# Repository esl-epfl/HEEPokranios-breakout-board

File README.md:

# This repository contains the HEEPokranios breakout board

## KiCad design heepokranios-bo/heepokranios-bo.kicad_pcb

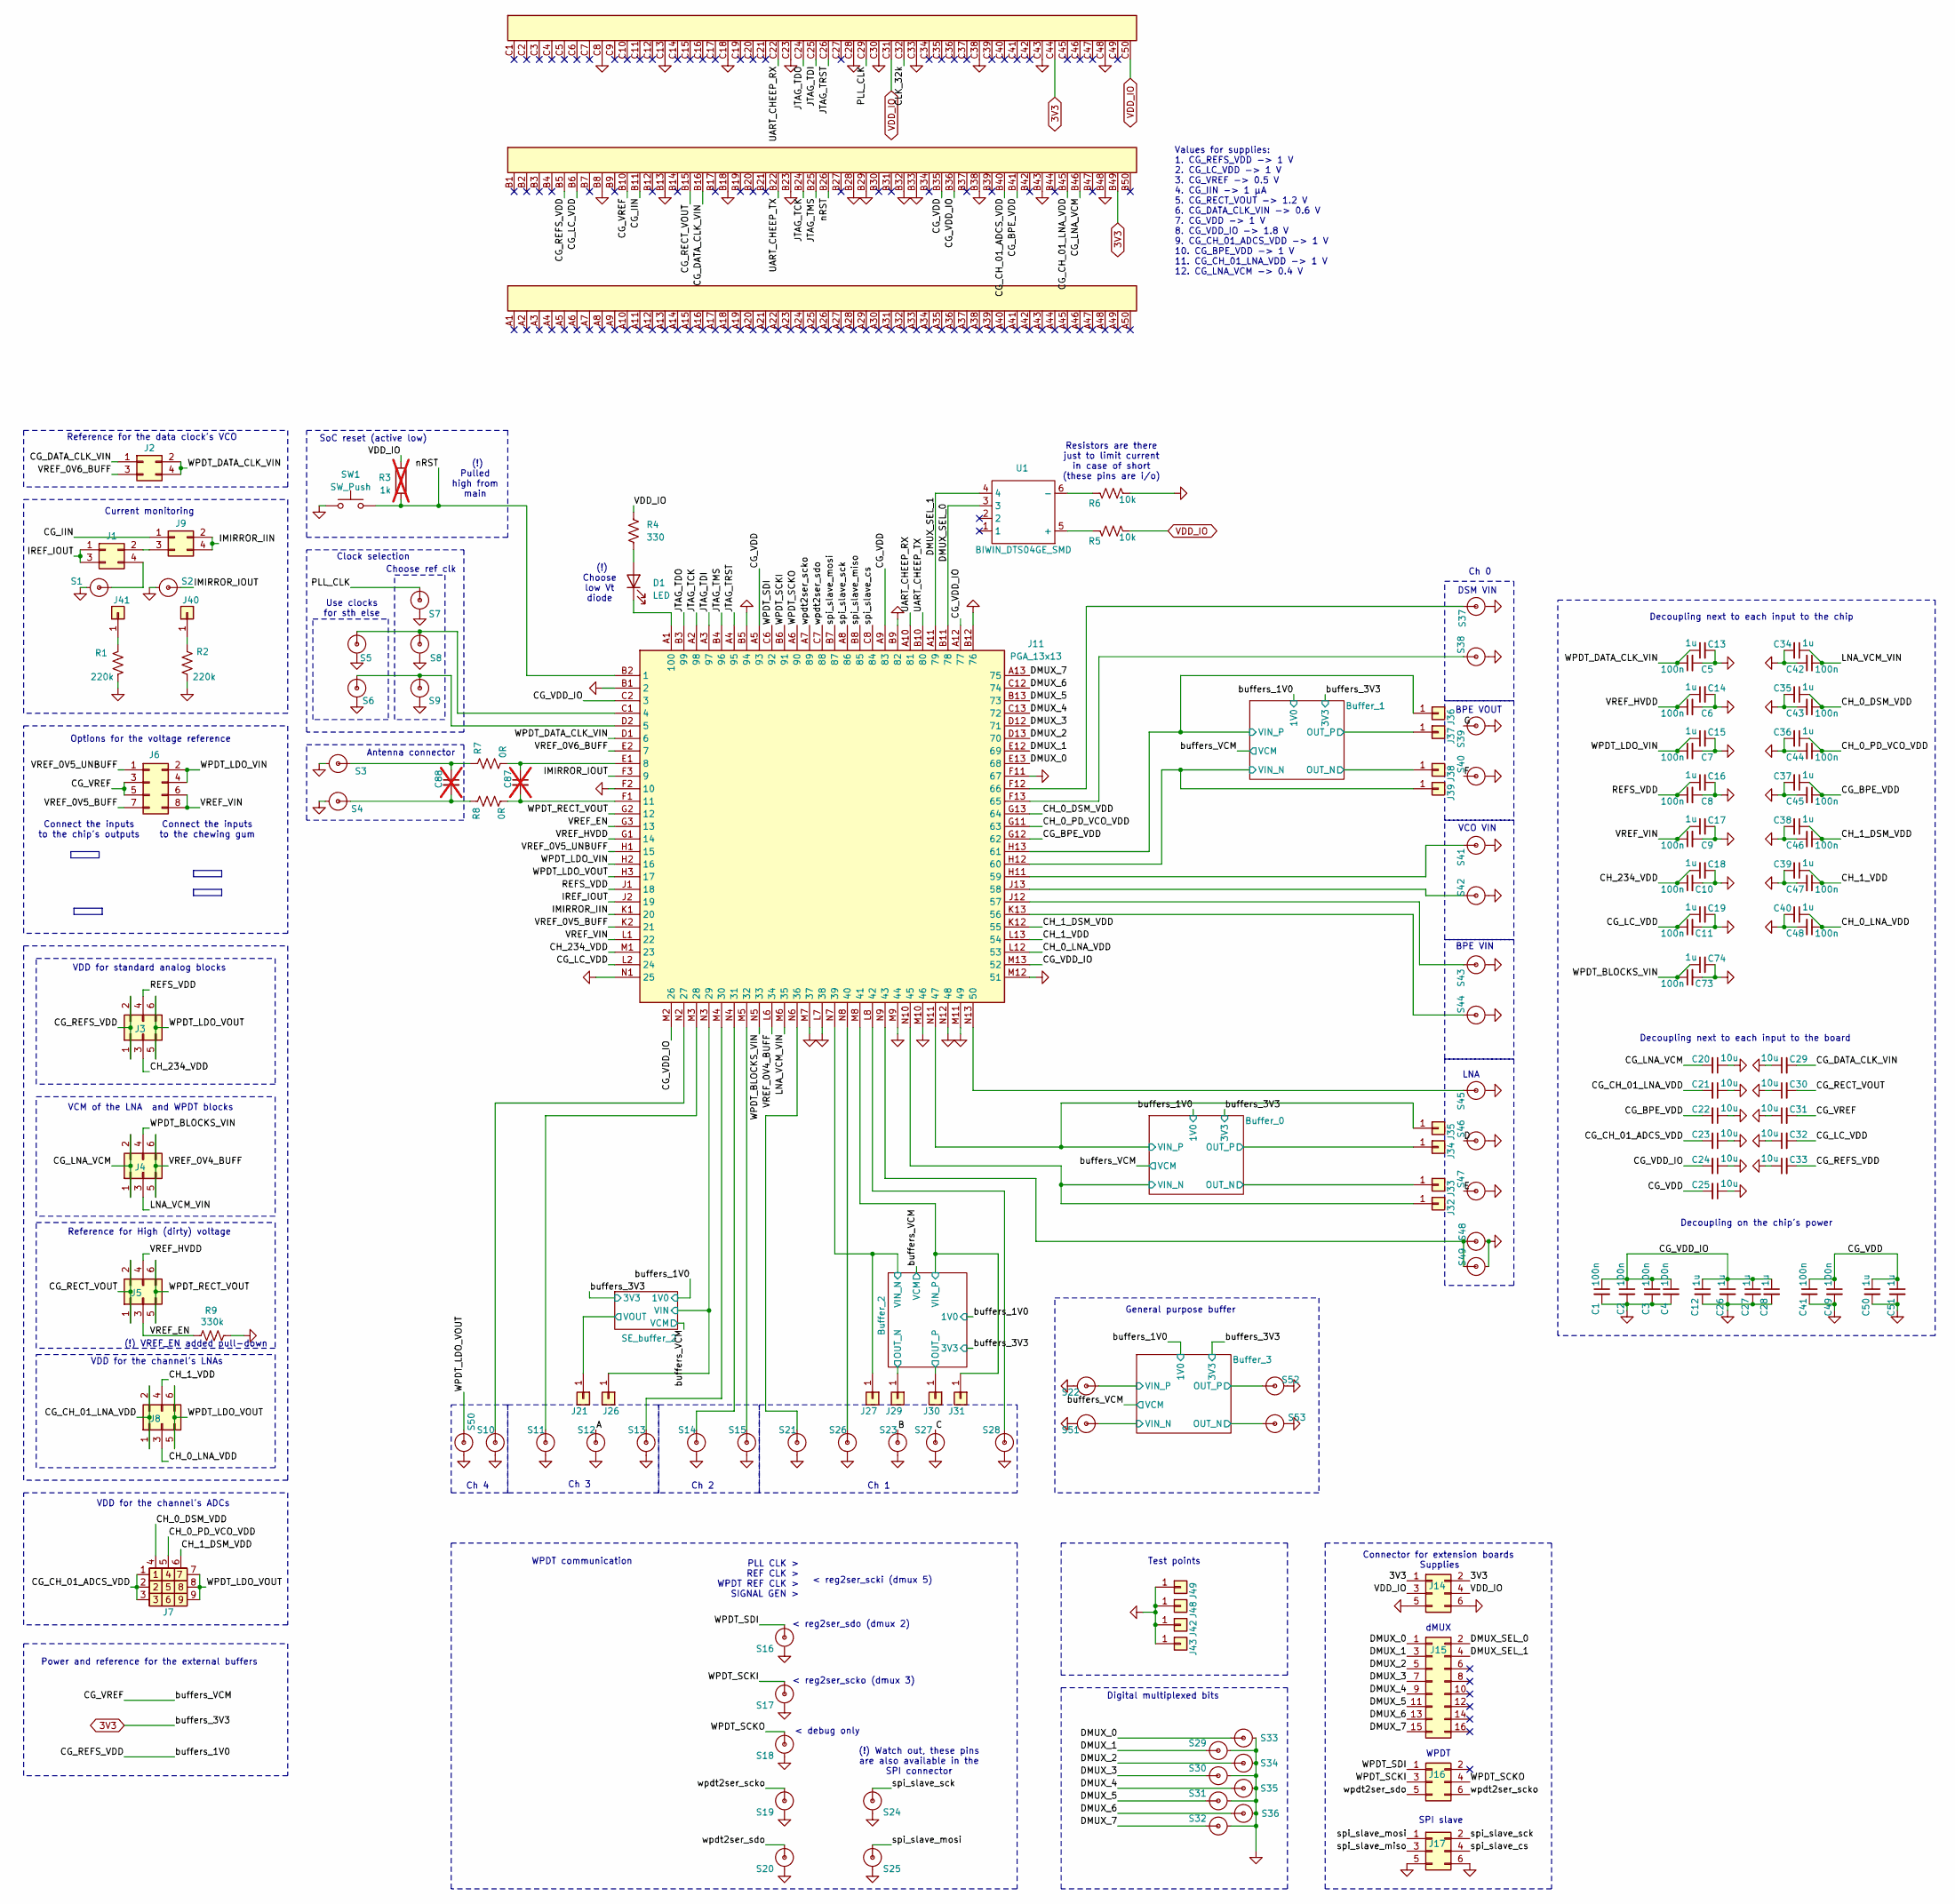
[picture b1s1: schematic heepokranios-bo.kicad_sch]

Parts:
C1, C2, C3, C4, C5, C6, C7, C8, C9, C10, C11, C41, C42, C43, C44, C45, C46, C47, C48, C49, C73: 100n; C_0603_1608Metric; Mouser Part Number 80-C0805C104Z3V; Digikey Part Number 399-9158-1-ND
C12, C13, C14, C15, C16, C17, C18, C19, C26, C27, C28, C34, C35, C36, C37, C38, C39, C40, C50, C51, C74: 1u; C_0603_1608Metric; Mouser Part Number 80-C0805C104Z3V; Digikey Part Number 399-9158-1-ND
C20, C21, C22, C23, C24, C25, C29, C30, C31, C32, C33: 10u; C_0603_1608Metric; Mouser Part Number 80-C0805C104Z3V; Digikey Part Number 399-9158-1-ND
C87, C88: C_0805_2012Metric_Pad1.18x1.45mm_HandSolder; Mouser Part Number 80-C0805C104Z3V; Digikey Part Number 399-9158-1-ND; not fitted
D1: LED; LED_0603_1608Metric
J1, J2, J9: Conn_02x02_Odd_Even; PinHeader_2x02_P2.54mm_Vertical
J3, J4, J5, J8: Conn_02x03_Odd_Even; PinHeader_2x03_P2.54mm_Vertical
J6: Conn_02x04_Odd_Even; PinHeader_2x04_P2.54mm_Vertical
J7: Conn_3x03
J10: cheep_board_connector
J11: PGA_13x13; Mouser Part Number 535-100-PGM13061-10
J14, J16, J17: Conn_02x03_Odd_Even; PinSocket_2x03_P2.54mm_Horizontal
J15: Conn_02x08_Odd_Even; PinSocket_2x08_P2.54mm_Horizontal
J21, J26, J27, J29, J30, J31, J32, J33, J34, J35, J36, J37, J38, J39, J40, J41, J42, J43, J48, J49: Conn_01x02; PinHeader_1x01_P2.54mm_Vertical
R1, R2: 220k; R_0603_1608Metric
R3: 1k; R_0603_1608Metric; LCSC C21190; not fitted
R4: 330; R_0603_1608Metric
R5, R6: 10k; R_0603_1608Metric
R7, R8: 0R; R_0603_1608Metric
R9: 330k; R_0603_1608Metric
S1, S2, S3, S4, S5, S6, S7, S8, S9, S10, S11, S12, S13, S14, S15, S16, S17, S18, S19, S20, S21, S22, S23, S24, S25, S26, S27, S28, S29, S30, S31, S32, S33, S34, S35, S36, S37, S38, S39, S40, S41, S42, S43, S44, S45, S46, S47, S48, S49, S50, S51, S52, S53: SMA connector; SMA_w_tp
SW1: SW_Push; SW_Push_1P1T_NO_CK_KMR2
U1: BIWIN_DTS04GE_SMD; lcsc C3294670

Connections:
3V3: J10.B49, J10.C44, J14.1, J14.2; also elsewhere on the board
/A: S12.1
/B: S23.1
/Buffer_0/OUT_N: J33.1 (Pin_1_1); also elsewhere on the board
/Buffer_0/OUT_P: J34.1 (Pin_1_1); also elsewhere on the board
/Buffer_0/VIN_N: J11.N10 (45), J32.1 (Pin_1_1); also elsewhere on the board
/Buffer_0/VIN_P: J11.N11 (47), J35.1 (Pin_1_1); also elsewhere on the board
/Buffer_1/OUT_N: J38.1 (Pin_1_1); also elsewhere on the board
/Buffer_1/OUT_P: J37.1 (Pin_1_1); also elsewhere on the board
/Buffer_1/VIN_N: J11.H12 (60), J39.1 (Pin_1_1); also elsewhere on the board
/Buffer_1/VIN_P: J11.H13 (61), J36.1 (Pin_1_1); also elsewhere on the board
/Buffer_2/OUT_N: J29.1 (Pin_1_1); also elsewhere on the board
/Buffer_2/OUT_P: J30.1 (Pin_1_1); also elsewhere on the board
/Buffer_2/VIN_N: J11.N7 (39), J27.1 (Pin_1_1); also elsewhere on the board
/Buffer_2/VIN_P: J11.M8 (41), J31.1 (Pin_1_1); also elsewhere on the board
/Buffer_3/OUT_N: S53.1; also elsewhere on the board
/Buffer_3/OUT_P: S52.1; also elsewhere on the board
/Buffer_3/VIN_N: S51.1; also elsewhere on the board
/Buffer_3/VIN_P: S22.1; also elsewhere on the board
/C: S27.1
/CG_BPE_VDD: C22.2, C37.1, C45.1, J10.B41, J11.G12 (62)
/CG_CH_01_ADCS_VDD: C23.2, J7.1, J7.2, J7.3, J10.B40
/CG_CH_01_LNA_VDD: C21.2, J8.1, J8.2, J10.B45
/CG_DATA_CLK_VIN: C29.2, J2.1, J10.B16
/CG_IIN: J9.1, J10.B11
/CG_LC_VDD: C11.1, C19.1, C32.2, J10.B6, J11.L2 (24)
/CG_LNA_VCM: C20.2, J4.1, J4.2, J10.B46
/CG_RECT_VOUT: C30.2, J5.1, J5.2, J10.B15
/CG_REFS_VDD: C33.2, J3.1, J3.2, J10.B5; also elsewhere on the board
/CG_VDD: C25.2, C41.1, C49.1, C50.1, C51.1, J10.B35, J11.A5 (93), J11.A9 (83)
/CG_VDD_IO: C1.1, C2.1, C3.1, C4.1, C12.1, C24.2, C26.1, C27.1, C28.1, J10.B36, J11.A12 (77), J11.C2 (3), J11.M2 (26), J11.M13 (52)
/CG_VREF: C31.2, J6.3, J6.5, J10.B10; also elsewhere on the board
/CH_0_DSM_VDD: C35.1, C43.1, J7.4, J11.G13 (64)
/CH_0_LNA_VDD: C40.1, C48.1, J8.3, J11.L12 (53)
/CH_0_PD_VCO_VDD: C36.1, C44.1, J7.5, J11.G11 (63)
/CH_1_DSM_VDD: C38.1, C46.1, J7.6, J11.K12 (55)
/CH_1_VDD: C39.1, C47.1, J8.4, J11.L13 (54)
/CH_234_VDD: C10.1, C18.1, J3.3, J11.M1 (23)
/CLK_32k: J10.C32
/D: S46.1
/DMUX_0: J11.E13 (68), J15.1, S33.1
/DMUX_1: J11.E12 (69), J15.3, S29.1
/DMUX_2: J11.D13 (70), J15.5, S34.1
/DMUX_3: J11.D12 (71), J15.7, S30.1
/DMUX_4: J11.C13 (72), J15.9, S35.1
/DMUX_5: J11.B13 (73), J15.11, S31.1
/DMUX_6: J11.C12 (74), J15.13, S36.1
/DMUX_7: J11.A13 (75), J15.15, S32.1
/DMUX_SEL_0: J11.B11 (78), J15.2, U1.3
/DMUX_SEL_1: J11.A11 (79), J15.4, U1.4
/E: S47.1
/F: S40.1
/G: S39.1
/IMIRROR_IIN: J9.2, J9.4, J11.K1 (20)
/IMIRROR_IOUT: J11.F3 (9), S2.1
/IREF_IOUT: J1.1, J1.3, J11.J2 (19)
/JTAG_TCK: J10.B24, J11.A2 (98)
/JTAG_TDI: J10.C25, J11.A3 (97)
/JTAG_TDO: J10.C24, J11.B3 (99)
/JTAG_TMS: J10.B25, J11.B4 (96)
/JTAG_TRST: J10.C26, J11.A4 (95)
/LNA_VCM_VIN: C34.1, C42.1, J4.3, J11.M6 (35)
/PLL_CLK: J10.C29, S7.1
/REFS_VDD: C8.1, C16.1, J3.4, J11.J1 (18)
/SE_buffer_2/VIN: J11.N3 (29), J26.1 (Pin_1_1); also elsewhere on the board
/SE_buffer_2/VOUT: J21.1 (Pin_1_1); also elsewhere on the board
/UART_CHEEP_RX: J10.C22, J11.A10 (81)
/UART_CHEEP_TX: J10.B22, J11.B10 (80)
/VREF_0V4_BUFF: J4.5, J4.6, J11.L6 (34)
/VREF_0V5_BUFF: J6.7, J11.K2 (21)
/VREF_0V5_UNBUFF: J6.1, J11.H1 (15)
/VREF_0V6_BUFF: J2.3, J11.E2 (7)
/VREF_EN: J5.3, J11.G3 (13), R9.1
/VREF_HVDD: C6.1, C14.1, J5.4, J11.G1 (14)
/VREF_VIN: C9.1, C17.1, J6.6, J6.8, J11.L1 (22)
/WPDT_BLOCKS_VIN: C73.1, C74.1, J4.4, J11.N5 (33)
/WPDT_DATA_CLK_VIN: C5.1, C13.1, J2.2, J2.4, J11.D1 (6)
/WPDT_LDO_VIN: C7.1, C15.1, J6.2, J6.4, J11.H2 (16)
/WPDT_LDO_VOUT: J3.5, J3.6, J7.7, J7.8, J7.9, J8.5, J8.6, J11.H3 (17), S50.1
/WPDT_RECT_VOUT: J5.5, J5.6, J11.G2 (12)
/WPDT_SCKI: J11.B6 (91), J16.3, S17.1
/WPDT_SCKO: J11.A6 (90), J16.4, S18.1
/WPDT_SDI: J11.C6 (92), J16.1, S16.1
/nRST: J10.B26, J11.B2 (1), R3.1, SW1.1
/spi_slave_cs: J11.C8 (84), J17.4
/spi_slave_miso: J11.B8 (85), J17.3
/spi_slave_mosi: J11.B7 (87), J17.1, S25.1
/spi_slave_sck: J11.A8 (86), J17.2, S24.1
/wpdt2ser_scko: J11.A7 (89), J16.6, S19.1
/wpdt2ser_sdo: J11.C7 (88), J16.5, S20.1
GND: C1.2, C2.2, C3.2, C4.2, C5.2, C6.2, C7.2, C8.2, C9.2, C10.2, C11.2, C12.2, C13.2, C14.2, C15.2, C16.2, C17.2, C18.2, C19.2, C20.1, C21.1, C22.1, C23.1, C24.1, C25.1, C26.2, C27.2, C28.2, C29.1, C30.1, C31.1, C32.1, C33.1, C34.2, C35.2, C36.2, C37.2, C38.2, C39.2, C40.2, C41.2, C42.2, C43.2, C44.2, C45.2, C46.2, C47.2, C48.2, C49.2, C50.2, C51.2, C73.2, C74.2, J10.B8, J10.B13, J10.B18, J10.B23, J10.B28, J10.B29, J10.B32, J10.B33, J10.B38, J10.B43, J10.B48, J10.C8, J10.C13, J10.C18, J10.C23, J10.C28, J10.C30, J10.C33, J10.C38, J10.C43, J10.C48, J11.B1 (2), J11.B5 (94), J11.B9 (82), J11.B12 (76), J11.F2 (10), J11.F11 (67), J11.L7 (38), J11.M7 (37), J11.M9 (44), J11.M10 (46), J11.M11 (49), J11.M12 (51), J11.N1 (25), J11.N12 (48), J14.5, J14.6, J17.5, J17.6, J42.1 (Pin_1_1), J43.1 (Pin_1_1), J48.1 (Pin_1_1), J49.1 (Pin_1_1), R1.2, R2.2, R6.2, R9.2, S1.2, S2.2, S3.2, S4.2, S5.2, S6.2, S7.2, S8.2, S9.2, S10.2, S11.2, S12.2, S13.2, S14.2, S15.2, S16.2, S17.2, S18.2, S19.2, S20.2, S21.2, S22.2, S23.2, S24.2, S25.2, S26.2, S27.2, S28.2, S29.2, S30.2, S31.2, S32.2, S33.2, S34.2, S35.2, S36.2, S37.2, S38.2, S39.2, S40.2, S41.2, S42.2, S43.2, S44.2, S45.2, S46.2, S47.2, S48.2, S49.2, S50.2, S51.2, S52.2, S53.2, SW1.2; also elsewhere on the board
unnamed: C88.1, R7.1, S3.1
unnamed: C88.2, R8.1, S4.1
unnamed: D1.2 (A), R4.2
unnamed: D1.1 (K), J11.A1 (100)
unnamed: J1.2, J9.3
unnamed: J1.4, S1.1
unnamed: J11.C1 (4), S5.1, S8.1
unnamed: J11.D2 (5), S6.1, S9.1
unnamed: C87.1, J11.E1 (8), R7.2
unnamed: C87.2, J11.F1 (11), R8.2
unnamed: J11.N2 (27), S10.1
unnamed: J11.M3 (28), S11.1
unnamed: J11.M4 (30), S13.1
unnamed: J11.N4 (31), S14.1
unnamed: J11.M5 (32), S15.1
unnamed: J11.N6 (36), S21.1
unnamed: J11.N8 (40), S26.1
unnamed: J11.L8 (42), S28.1
unnamed: J11.N9 (43), S48.1, S49.1
unnamed: J11.N13 (50), S45.1
unnamed: J11.K13 (56), S44.1
unnamed: J11.J12 (57), S43.1
unnamed: J11.J13 (58), S42.1
unnamed: J11.H11 (59), S41.1
unnamed: J11.F13 (65), S38.1
unnamed: J11.F12 (66), S37.1
unnamed: J40.1 (Pin_1_1), R2.1
unnamed: J41.1 (Pin_1_1), R1.1
unnamed: R5.1, U1.5 (+)
unnamed: R6.1, U1.6 (-)
VDD_IO: J10.C31, J10.C50, J14.3, J14.4, R3.2, R4.1, R5.2

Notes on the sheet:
LNA
Ch 1
Values for supplies: 1. CG_REFS_VDD -> 1 V 2. CG_LC_VDD -> 1 V 3. CG_VREF -> 0.5 V 4. CG_IIN -> 1 μA 5. CG_RECT_VOUT -> 1.2 V 6. CG_DATA_CLK_VIN -> 0.6 V 7. CG_VDD -> 1 V 8. CG_VDD_IO -> 1.8 V 9. CG_CH_01_ADCS_VDD -> 1 V 10. CG_BPE_VDD -> 1 V 11. CG_CH_01_LNA_VDD -> 1 V 12. CG_LNA_VCM -> 0.4 V
Digital multiplexed bits
(!) Choose low Vt diode
Ch 0
Clock selection
Connector for extension boards
WPDT communication
SPI slave
VCM of the LNA and WPDT blocks
Decoupling on the chip's power
PLL CLK > REF CLK > WPDT REF CLK > SIGNAL GEN >
Test points
VDD for the channel's ADCs
BPE VOUT
< reg2ser_scki (dmux 5)
< reg2ser_sdo (dmux 2)
Use clocks for sth else
Power and reference for the external buffers
VDD for standard analog blocks
Options for the voltage reference
Choose ref clk
< reg2ser_scko (dmux 3)
Current monitoring
Ch 2
dMUX
Ch 4
Decoupling next to each input to the chip
BPE VIN
SoC reset (active low)
Ch 3
VCO VIN
DSM VIN
< debug only
VDD for the channel's LNAs
(!) VREF_EN added pull-down
Reference for the data clock's VCO
Connect the inputs to the chewing gum
WPDT

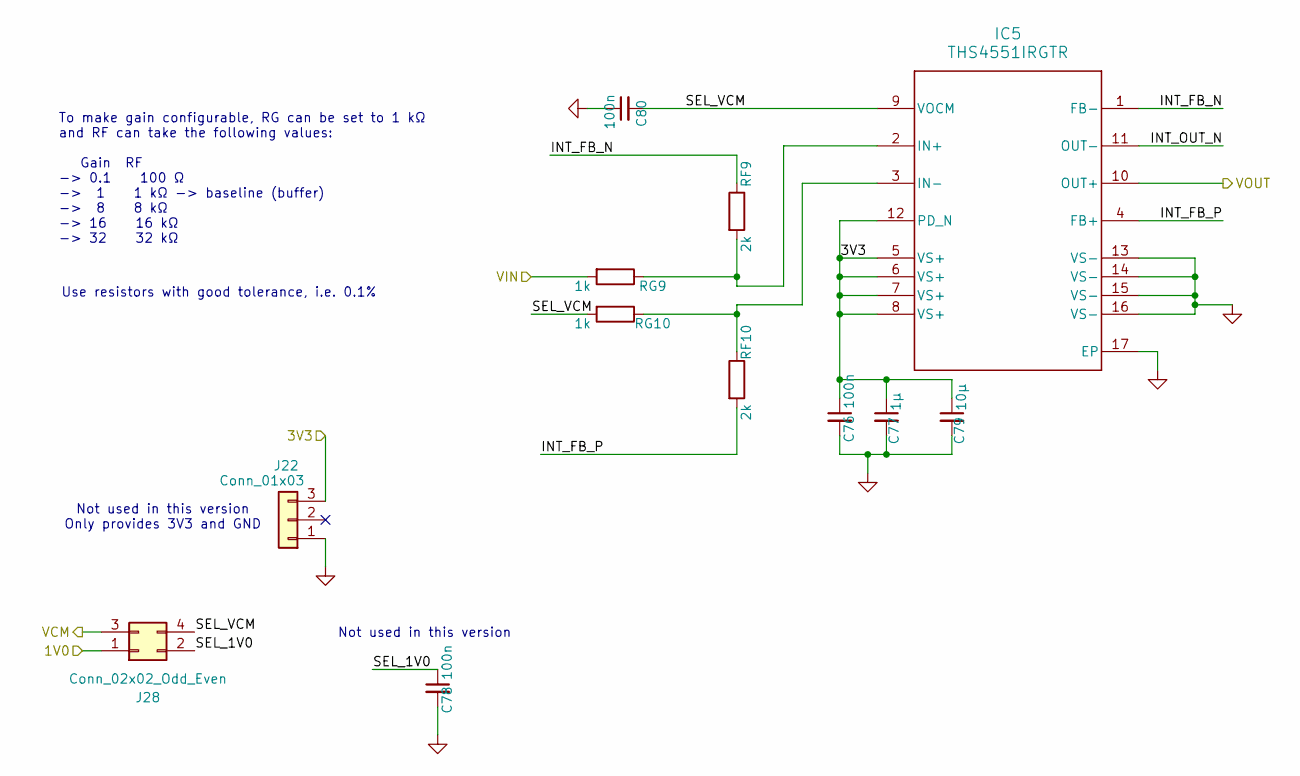
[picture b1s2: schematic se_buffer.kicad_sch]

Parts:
C76, C78, C80: 100n; C_0603_1608Metric; Mouser Part Number 80-C0805C104Z3V; Digikey Part Number 399-9158-1-ND
C77: 1μ; C_0603_1608Metric; Mouser Part Number 80-C0805C104Z3V; Digikey Part Number 399-9158-1-ND
C79: 10μ; C_0603_1608Metric; Mouser Part Number 80-C0805C104Z3V; Digikey Part Number 399-9158-1-ND
IC5: THS4551IRGTR; RGT0016C
J22: Conn_01x03; PinHeader_1x03_P2.54mm_Vertical
J28: Conn_02x02_Odd_Even; PinHeader_2x02_P2.54mm_Vertical
RF9, RF10: 2k; R_0603_1608Metric; LCSC C22975
RG9, RG10: 1k; R_0603_1608Metric; LCSC C22975

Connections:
3V3: C76.1, C77.1, C79.1, IC5.5 (VS+), IC5.6 (VS+), IC5.7 (VS+), IC5.8 (VS+), IC5.12 (PD_N), J22.3; also elsewhere on the board
/CG_REFS_VDD: J28.1; also elsewhere on the board
/CG_VREF: J28.3; also elsewhere on the board
/SE_buffer_2/INT_FB_N: IC5.1 (FB-), RF9.1
/SE_buffer_2/INT_FB_P: IC5.4 (FB+), RF10.2
/SE_buffer_2/INT_OUT_N: IC5.11 (OUT-)
/SE_buffer_2/SEL_1V0: C78.1, J28.2
/SE_buffer_2/SEL_VCM: C80.2, IC5.9 (VOCM), J28.4, RG10.2
/SE_buffer_2/VIN: RG9.2; also elsewhere on the board
/SE_buffer_2/VOUT: IC5.10 (OUT+); also elsewhere on the board
GND: C76.2, C77.2, C78.2, C79.2, C80.1, IC5.13 (VS-), IC5.14 (VS-), IC5.15 (VS-), IC5.16 (VS-), IC5.17 (EP), J22.1; also elsewhere on the board
unnamed: IC5.2 (IN+), RF9.2, RG9.1
unnamed: IC5.3 (IN-), RF10.1, RG10.1

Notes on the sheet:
To make gain configurable, RG can be set to 1 kΩ and RF can take the following values: Gain RF -> 0.1 100 Ω -> 1 1 kΩ -> baseline (buffer) -> 8 8 kΩ -> 16 16 kΩ -> 32 32 kΩ
Not used in this version Only provides 3V3 and GND
Not used in this version
Use resistors with good tolerance, i.e. 0.1%

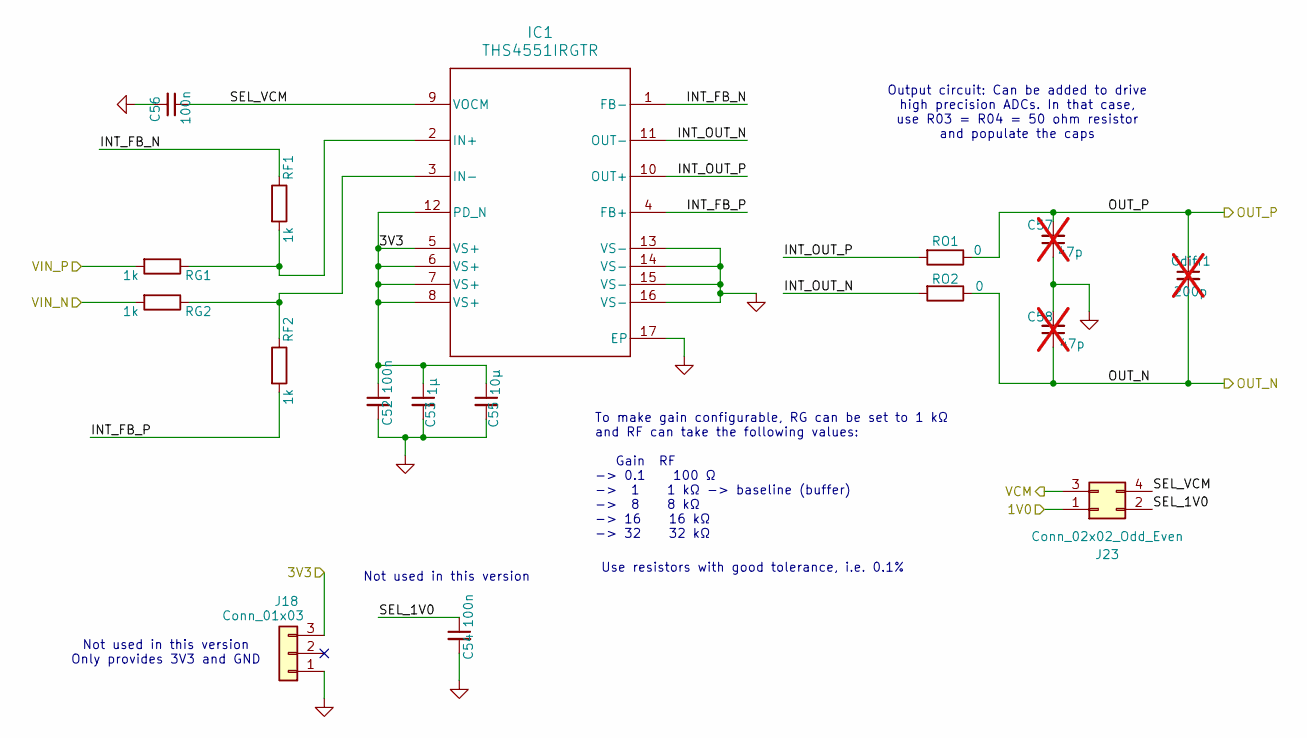
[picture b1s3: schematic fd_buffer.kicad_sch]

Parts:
C52, C54, C56: 100n; C_0603_1608Metric; Mouser Part Number 80-C0805C104Z3V; Digikey Part Number 399-9158-1-ND
C53: 1μ; C_0603_1608Metric; Mouser Part Number 80-C0805C104Z3V; Digikey Part Number 399-9158-1-ND
C55: 10μ; C_0603_1608Metric; Mouser Part Number 80-C0805C104Z3V; Digikey Part Number 399-9158-1-ND
C57, C58: 47p; C_0603_1608Metric; Mouser Part Number 80-C0805C104Z3V; Digikey Part Number 399-9158-1-ND; not fitted
Cdiff1: 200p; C_0603_1608Metric; Mouser Part Number 80-C0805C104Z3V; Digikey Part Number 399-9158-1-ND; not fitted
IC1: THS4551IRGTR; RGT0016C
J18: Conn_01x03; PinHeader_1x03_P2.54mm_Vertical
J23: Conn_02x02_Odd_Even; PinHeader_2x02_P2.54mm_Vertical
RF1, RF2: 1k; R_0603_1608Metric; LCSC C22975
RG1, RG2: 1k; R_0603_1608Metric; LCSC C22975
RO1, RO2: 0; R_0603_1608Metric; LCSC C22975

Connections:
3V3: C52.1, C53.1, C55.1, IC1.5 (VS+), IC1.6 (VS+), IC1.7 (VS+), IC1.8 (VS+), IC1.12 (PD_N), J18.3; also elsewhere on the board
/Buffer_0/INT_FB_N: IC1.1 (FB-), RF1.1
/Buffer_0/INT_FB_P: IC1.4 (FB+), RF2.2
/Buffer_0/INT_OUT_N: IC1.11 (OUT-), RO2.2
/Buffer_0/INT_OUT_P: IC1.10 (OUT+), RO1.2
/Buffer_0/OUT_N: C58.1, Cdiff1.2, RO2.1; also elsewhere on the board
/Buffer_0/OUT_P: C57.2, Cdiff1.1, RO1.1; also elsewhere on the board
/Buffer_0/SEL_1V0: C54.1, J23.2
/Buffer_0/SEL_VCM: C56.1, IC1.9 (VOCM), J23.4
/Buffer_0/VIN_N: RG2.2; also elsewhere on the board
/Buffer_0/VIN_P: RG1.2; also elsewhere on the board
/CG_REFS_VDD: J23.1; also elsewhere on the board
/CG_VREF: J23.3; also elsewhere on the board
GND: C52.2, C53.2, C54.2, C55.2, C56.2, C57.1, C58.2, IC1.13 (VS-), IC1.14 (VS-), IC1.15 (VS-), IC1.16 (VS-), IC1.17 (EP), J18.1; also elsewhere on the board
unnamed: IC1.2 (IN+), RF1.2, RG1.1
unnamed: IC1.3 (IN-), RF2.1, RG2.1

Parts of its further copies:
C59, C61, C63, C66, C68, C70, C75, C82, C84: 100n; C_0603_1608Metric; Mouser Part Number 80-C0805C104Z3V; Digikey Part Number 399-9158-1-ND
C60, C67, C81: 1μ; C_0603_1608Metric; Mouser Part Number 80-C0805C104Z3V; Digikey Part Number 399-9158-1-ND
C62, C69, C83: 10μ; C_0603_1608Metric; Mouser Part Number 80-C0805C104Z3V; Digikey Part Number 399-9158-1-ND
C64, C65, C71, C72, C85, C86: 47p; C_0603_1608Metric; Mouser Part Number 80-C0805C104Z3V; Digikey Part Number 399-9158-1-ND; not fitted
Cdiff2, Cdiff3, Cdiff4: 200p; C_0603_1608Metric; Mouser Part Number 80-C0805C104Z3V; Digikey Part Number 399-9158-1-ND; not fitted
IC2, IC3, IC4: THS4551IRGTR; RGT0016C
J19, J20, J45: Conn_01x03; PinHeader_1x03_P2.54mm_Vertical
J24, J25, J44: Conn_02x02_Odd_Even; PinHeader_2x02_P2.54mm_Vertical
RF3, RF4, RF5, RF6, RF7, RF8: 1k; R_0603_1608Metric; LCSC C22975
RG3, RG4, RG5, RG6, RG7, RG8: 1k; R_0603_1608Metric; LCSC C22975
RO3, RO4, RO5, RO6, RO7, RO8: 0; R_0603_1608Metric; LCSC C22975

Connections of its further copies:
3V3: C59.1, C60.1, C62.1, C66.1, C67.1, C69.1, C75.1, C81.1, C83.1, IC2.5 (VS+), IC2.6 (VS+), IC2.7 (VS+), IC2.8 (VS+), IC2.12 (PD_N), IC3.5 (VS+), IC3.6 (VS+), IC3.7 (VS+), IC3.8 (VS+), IC3.12 (PD_N), IC4.5 (VS+), IC4.6 (VS+), IC4.7 (VS+), IC4.8 (VS+), IC4.12 (PD_N), J19.3, J20.3, J45.3; also elsewhere on the board
/Buffer_1/INT_FB_N: IC2.1 (FB-), RF3.1
/Buffer_1/INT_FB_P: IC2.4 (FB+), RF4.2
/Buffer_1/INT_OUT_N: IC2.11 (OUT-), RO4.2
/Buffer_1/INT_OUT_P: IC2.10 (OUT+), RO3.2
/Buffer_1/OUT_N: C65.1, Cdiff2.2, RO4.1; also elsewhere on the board
/Buffer_1/OUT_P: C64.2, Cdiff2.1, RO3.1; also elsewhere on the board
/Buffer_1/SEL_1V0: C61.1, J24.2
/Buffer_1/SEL_VCM: C63.1, IC2.9 (VOCM), J24.4
/Buffer_1/VIN_N: RG4.2; also elsewhere on the board
/Buffer_1/VIN_P: RG3.2; also elsewhere on the board
/Buffer_2/INT_FB_N: IC3.1 (FB-), RF5.1
/Buffer_2/INT_FB_P: IC3.4 (FB+), RF6.2
/Buffer_2/INT_OUT_N: IC3.11 (OUT-), RO6.2
/Buffer_2/INT_OUT_P: IC3.10 (OUT+), RO5.2
/Buffer_2/OUT_N: C72.1, Cdiff3.2, RO6.1; also elsewhere on the board
/Buffer_2/OUT_P: C71.2, Cdiff3.1, RO5.1; also elsewhere on the board
/Buffer_2/SEL_1V0: C68.1, J25.2
/Buffer_2/SEL_VCM: C70.1, IC3.9 (VOCM), J25.4
/Buffer_2/VIN_N: RG6.2; also elsewhere on the board
/Buffer_2/VIN_P: RG5.2; also elsewhere on the board
/Buffer_3/INT_FB_N: IC4.1 (FB-), RF7.1
/Buffer_3/INT_FB_P: IC4.4 (FB+), RF8.2
/Buffer_3/INT_OUT_N: IC4.11 (OUT-), RO8.2
/Buffer_3/INT_OUT_P: IC4.10 (OUT+), RO7.2
/Buffer_3/OUT_N: C86.1, Cdiff4.2, RO8.1; also elsewhere on the board
/Buffer_3/OUT_P: C85.2, Cdiff4.1, RO7.1; also elsewhere on the board
/Buffer_3/SEL_1V0: C82.1, J44.2
/Buffer_3/SEL_VCM: C84.1, IC4.9 (VOCM), J44.4
/Buffer_3/VIN_N: RG8.2; also elsewhere on the board
/Buffer_3/VIN_P: RG7.2; also elsewhere on the board
/CG_REFS_VDD: J24.1, J25.1, J44.1; also elsewhere on the board
/CG_VREF: J24.3, J25.3, J44.3; also elsewhere on the board
GND: C59.2, C60.2, C61.2, C62.2, C63.2, C64.1, C65.2, C66.2, C67.2, C68.2, C69.2, C70.2, C71.1, C72.2, C75.2, C81.2, C82.2, C83.2, C84.2, C85.1, C86.2, IC2.13 (VS-), IC2.14 (VS-), IC2.15 (VS-), IC2.16 (VS-), IC2.17 (EP), IC3.13 (VS-), IC3.14 (VS-), IC3.15 (VS-), IC3.16 (VS-), IC3.17 (EP), IC4.13 (VS-), IC4.14 (VS-), IC4.15 (VS-), IC4.16 (VS-), IC4.17 (EP), J19.1, J20.1, J45.1; also elsewhere on the board
unnamed: IC2.2 (IN+), RF3.2, RG3.1
unnamed: IC2.3 (IN-), RF4.1, RG4.1
unnamed: IC3.2 (IN+), RF5.2, RG5.1
unnamed: IC3.3 (IN-), RF6.1, RG6.1
unnamed: IC4.2 (IN+), RF7.2, RG7.1
unnamed: IC4.3 (IN-), RF8.1, RG8.1

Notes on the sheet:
Use resistors with good tolerance, i.e. 0.1%
Not used in this version Only provides 3V3 and GND
Output circuit: Can be added to drive high precision ADCs. In that case, use R03 = R04 = 50 ohm resistor and populate the caps
To make gain configurable, RG can be set to 1 kΩ and RF can take the following values: Gain RF -> 0.1 100 Ω -> 1 1 kΩ -> baseline (buffer) -> 8 8 kΩ -> 16 16 kΩ -> 32 32 kΩ
Not used in this version

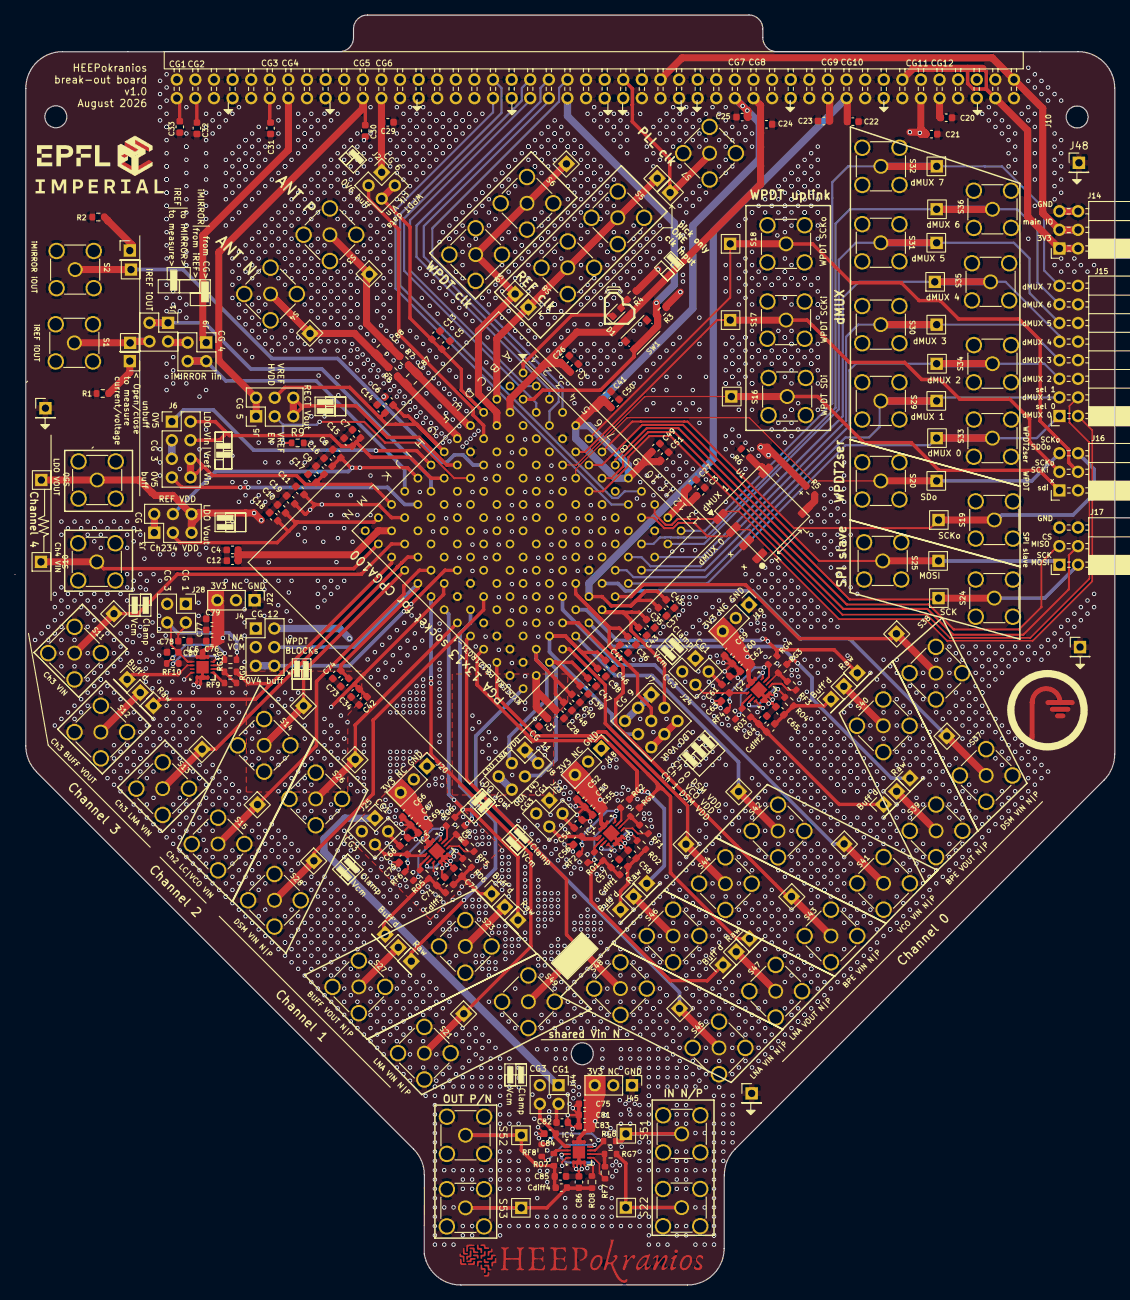
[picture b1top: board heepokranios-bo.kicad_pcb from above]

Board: 4 copper layers, 150.1 x 173.4 mm, 235 parts (0 on the bottom side), 152 nets.

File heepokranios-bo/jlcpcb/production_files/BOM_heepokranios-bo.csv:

Comment,Designator,Footprint,LCSC,Qty
100n,"C1,C2,C3,C4,C5,C6,C7,C8,C9,C10,C11,C41,C42,C43,C44,C45,C46,C47,C48,C49,C52,C54,C56,C59,C61,C63,C66,C68,C70,C73,C75,C76,C78,C80,C82,C84",C_0603_1608Metric,C30926,36
1u,"C12,C13,C14,C15,C16,C17,C18,C19,C26,C27,C28,C34,C35,C36,C37,C38,C39,C40,C50,C51,C74,C53,C60,C67,C77,C81",C_0603_1608Metric,C15849,26
10u,"C20,C21,C22,C23,C24,C25,C29,C30,C31,C32,C33,C55,C62,C69,C79,C83",C_0603_1608Metric,C19702,16
LED,D1,LED_0603_1608Metric,C84263,1
ADA4945-1ACPZ-R7,"IC1,IC2,IC3,IC4,IC5",QFN50P300X300X80-17N-D,C560261,5
Conn_02x02_Odd_Even,"J1,J2,J9,J23,J24,J25,J28,J44",PinHeader_2x02_P2.54mm_Vertical,C66690,8
Conn_02x03_Odd_Even,"J3,J4,J5,J8",PinHeader_2x03_P2.54mm_Vertical,C42431837,4
Conn_02x03_Odd_Even,"J14,J16,J17",PinSocket_2x03_P2.54mm_Horizontal,C5333425,3
Conn_02x04_Odd_Even,J6,PinHeader_2x04_P2.54mm_Vertical,C7430400,1
Conn_03x03,J7,PinHeader_3x03_P2.54mm_Vertical,C7429377,1
Conn_02x08_Odd_Even,J15,PinSocket_2x08_P2.54mm_Horizontal,C239359,1
Conn_01x03,"J18,J19,J20,J22,J45",PinHeader_1x03_P2.54mm_Vertical,C42431836,5
220k,"R1,R2",R_0603_1608Metric,C22961,2
10k,"R5,R6",R_0603_1608Metric,C2930027,2
2k,"RF9,RF10",R_0603_1608Metric,C2907022,2
1k,"RG1,RG2,RG3,RG4,RG5,RG6,RG7,RG8,RG9,RG10,RF1,RF2,RF3,RF4,RF5,RF6,RF7,RF8",R_0603_1608Metric,C110776,18
0,"RO1,RO2,RO3,RO4,RO5,RO6,RO7,RO8,R7,R8",R_0603_1608Metric,C2906974,10
SMA connector,"S1,S2,S3,S4,S5,S6,S7,S8,S9,S10,S11,S12,S13,S14,S15,S16,S17,S18,S19,S20,S21,S22,S23,S24,S25,S26,S27,S28,S29,S30,S31,S32,S33,S34,S35,S36,S37,S38,S39,S40,S41,S42,S43,S44,S45,S46,S47,S48,S49,S50,S51,S52,S53",SMA_w_tp,C2987686,53
SW_Push,SW1,SW_Push_1P1T_NO_CK_KMR2,C221678,1
BIWIN_DTS04GE_SMD,U1,BIWIN_DTS04GE_SMD,C3294670,1
330,R4,R_0603_1608Metric,C125768,1
330k,R9,R_0603_1608Metric,C23137,1

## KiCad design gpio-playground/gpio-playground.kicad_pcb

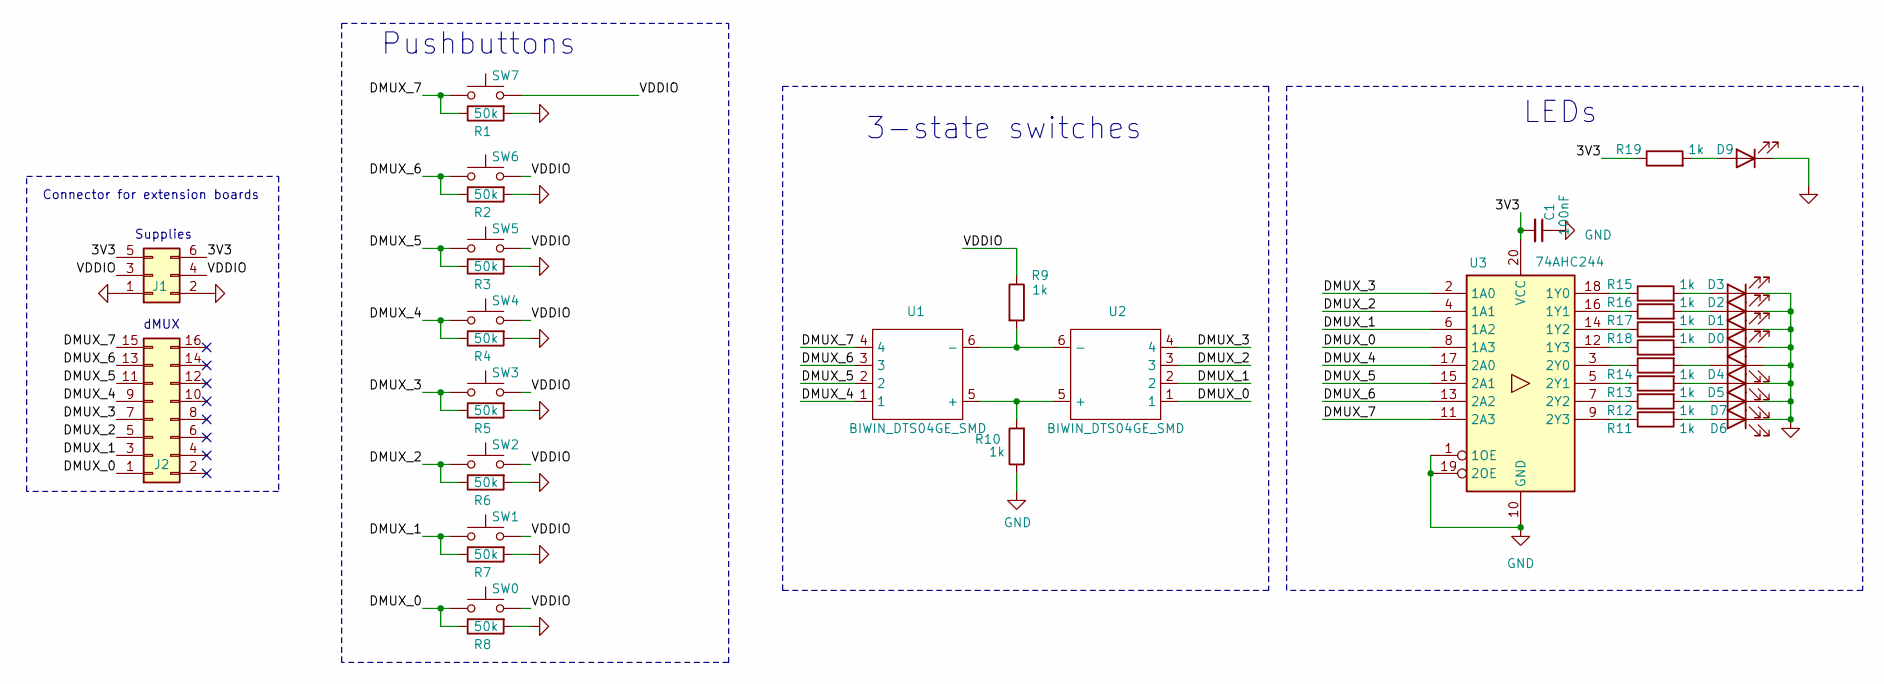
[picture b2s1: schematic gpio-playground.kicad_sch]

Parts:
C1: 100nF; C_0603_1608Metric; Mouser Part Number 80-C0805C104Z3V; Digikey Part Number 399-9158-1-ND
D0, D1, D2, D3, D4, D5, D6: LED; LED_0603_1608Metric; LCSC C965804
D7: LED; LED_0603_1608Metric; LCSC C84266
D9: LED; LED_0603_1608Metric; LCSC C84263
J1: Conn_02x03_Odd_Even; PinHeader_2x03_P2.54mm_Horizontal
J2: Conn_02x08_Odd_Even; PinHeader_2x08_P2.54mm_Horizontal
R1, R2, R3, R4, R5, R6, R7, R8: 50k; R_0603_1608Metric; LCSC C21190
R9, R10, R11, R12, R13, R14, R15, R16, R17, R18: 1k; R_0603_1608Metric; LCSC C21190
R19: 1k; R_0603_1608Metric; LCSC C22975
SW0, SW1, SW2, SW3, SW4, SW5, SW6, SW7: SW_Push; SW_Push_1P1T_NO_CK_KMR2; LCSC C221678
U1, U2: BIWIN_DTS04GE_SMD; lcsc C3294670
U3: 74AHC244; TSSOP-20_4.4x6.5mm_P0.65mm; LCSC C7475

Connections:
/3V3: C1.2, J1.5, J1.6, R19.1, U3.20 (VCC)
/DMUX_0: J2.1, R8.1, SW0.1, U2.1, U3.8 (1A3)
/DMUX_1: J2.3, R7.1, SW1.1, U2.2, U3.6 (1A2)
/DMUX_2: J2.5, R6.1, SW2.1, U2.3, U3.4 (1A1)
/DMUX_3: J2.7, R5.1, SW3.1, U2.4, U3.2 (1A0)
/DMUX_4: J2.9, R4.1, SW4.1, U1.1, U3.17 (2A0)
/DMUX_5: J2.11, R3.1, SW5.1, U1.2, U3.15 (2A1)
/DMUX_6: J2.13, R2.1, SW6.1, U1.3, U3.13 (2A2)
/DMUX_7: J2.15, R1.1, SW7.1, U1.4, U3.11 (2A3)
/VDDIO: J1.3, J1.4, R9.1, SW0.2, SW1.2, SW2.2, SW3.2, SW4.2, SW5.2, SW6.2, SW7.2
GND: C1.1, D0.1 (K), D1.1 (K), D2.1 (K), D3.1 (K), D4.1 (K), D5.1 (K), D6.1 (K), D7.1 (K), D9.1 (K), J1.1, J1.2, R1.2, R2.2, R3.2, R4.2, R5.2, R6.2, R7.2, R8.2, R10.1, U3.1 (1OE), U3.10 (GND), U3.19 (2OE)
unnamed: D0.2 (A), R18.2
unnamed: D1.2 (A), R17.2
unnamed: D2.2 (A), R16.2
unnamed: D3.2 (A), R15.2
unnamed: D4.2 (A), R14.2
unnamed: D5.2 (A), R13.2
unnamed: D6.2 (A), R12.2
unnamed: D7.2 (A), R11.2
unnamed: D9.2 (A), R19.2
unnamed: R10.2, U1.5 (+), U2.5 (+)
unnamed: R9.2, U1.6 (-), U2.6 (-)
unnamed: R15.1, U3.18 (1Y0)
unnamed: R16.1, U3.16 (1Y1)
unnamed: R17.1, U3.14 (1Y2)
unnamed: R18.1, U3.12 (1Y3)
unnamed: R14.1, U3.3 (2Y0)
unnamed: R13.1, U3.5 (2Y1)
unnamed: R12.1, U3.7 (2Y2)
unnamed: R11.1, U3.9 (2Y3)

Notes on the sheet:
Pushbuttons
Supplies
Connector for extension boards
dMUX
LEDs
3-state switches

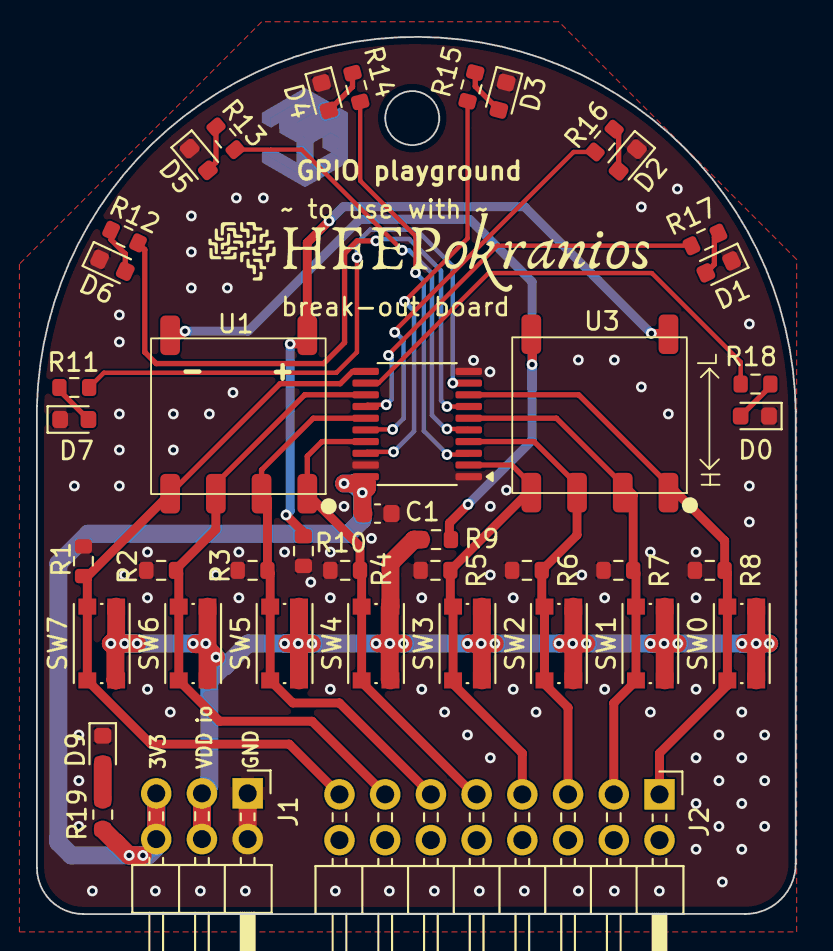
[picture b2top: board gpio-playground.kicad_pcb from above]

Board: 2 copper layers, 42.2 x 48.7 mm, 42 parts (0 on the bottom side), 30 nets.

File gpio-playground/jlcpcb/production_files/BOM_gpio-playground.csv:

Comment,Designator,Footprint,LCSC,Qty
100n,C1,C_0603_1608Metric,C30926,1
LED,"D0,D1,D2,D3,D4,D5,D6,D7,D9",LED_0603_1608Metric,C84263,9
Conn_02x03_Odd_Even,J1,PinHeader_2x03_P2.54mm_Horizontal,C41417351,1
Conn_02x08_Odd_Even,J2,PinHeader_2x08_P2.54mm_Horizontal,C41417356,1
50k,"R1,R2,R3,R4,R5,R6,R7,R8",R_0603_1608Metric,C861451,8
1k,"R9,R10,R11,R12,R13,R14,R15,R16,R17,R18,R19",R_0603_1608Metric,C110776,11
SW_Push,"SW0,SW1,SW2,SW3,SW4,SW5,SW6,SW7",SW_Push_1P1T_NO_CK_KMR2,C221678,8
BIWIN_DTS04GE_SMD,"U1,U2",BIWIN_DTS04GE_SMD,C3294670,2
74AHC244,U3,TSSOP-20_4.4x6.5mm_P0.65mm,C7475,1
